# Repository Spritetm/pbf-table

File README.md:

# Pinball Fantasies physical virtual pinball table

These are the firmware, case designs, schematics and PCB artwork
for the tiny video pinball table as described [here](https://spritesmods.com?art=pftable).

# Firmware

The firmware consists of a core emulator that emulates the main game
logic, a music player to replace the audio subsystem, and bindings
for graphics, input, and audio playback for various situations.

There are three builds for the firmware:

- Host build. For this, make sure you have the SDL2 development libraries
  installed and run ``make`` ``in the esp32/components/emu`` folder. You
  should get an ``emu`` binary using that. Use lshift, rshift, F1 and 
  enter to control the emulator.
- ESP32 build for ESP-Wrover-Kit
  This needs a wrover with >=8MiB of flash (and >=2MiB of psram). Use
  ``idf.py set-target esp32`` to select this and build and flash 
  using standard esp-idf procedures. You need buttons to control these,
  for start, plunger, left flipper and right flipper respectively, 
  connect buttons from GPIO 14, 13, 15 and 12 to ground. Audio signal
  comes out of GPIO26. Note that the game does not run at full frame
  rate on an ESP32 as the code is not optimized for that chip.
- ESP32S3 on custom PCB.
  This needs the pcbs from the ``pcb/`` and ``pcb-backbox-large/`` fabricated
  and assembled. Use ``idf.py set-target esp32s3`` and build and flash
  according to standard esp-idf procedures.

Note that the ESP32 and ESP32-S3 targets also need the Pinball 
Fantasies data files flashed; the Unix build simply needs them to
exist in the data directory. Details and helpers for obtaining these
files is in the ``data/README.md`` file. There is an example script for
flashing in ``esp32/flashdata.sh``, but it may need modifying for your
particular setup.

# Case

There is a case design (made in OpenSCAD) in the ``case`` subdirectory. 
Note that the measures are mostly what works on my 3d-printer; you 
may need to print this, see if it fits, then print again to get a 
working case.

The case parts are held together by two m3 screws fitting in two 4x5mm
brass screw thread inserts. I simply super-glued the inserts in place.

# PCB

There are three folders with Kicad PCBs: ``pcb``, ``pcb-backboard`` and 
``pcb-backboard-large``. ``pcb`` contains the main PCB which fits under
the main playfield LCD. ``pcb-backboard-large`` contains the PCB I used
for the final backboard, it interfaces with a 2.3" 320x240 LCD. ``pcb-backboard``
is a previous iteration of this; it has an 1.5" 240x240 LCD on it; it 
is included for reference only.

Note: You must use an ESP32-S3 module that has 2 or more megabyte of
QUAD PSRAM onboard. A module with octal PSRAM (or octal flash) will
not function, as it needs GPIOs that are used for other things.

# Components

Most of the components are indicated on the PCBs, but some are connected
using JST-PH or JST-XH connectors. Here's a short list of what goes where:

- J2: Speaker. I used a 4 ohm, 1.5W speaker from a laptop I had around.
- J3: Connected to an 10uF MLCC SMD cap used as the plunger sensor. The 
  plunger mechanics physically hit this cap when slamming back. See
  article on how that works.
- J4: LiIon/LiPo battery. I used a generic 1000mAh, 3.7V cell I had around.
- J5: Horizontal and vertical linear haptic actuators. These actuators are
  spare parts for a Huawei Mate 30 Pro.
- J6: Flipper and start buttons. These are a 4*5.6 HD11 microswitch each.
  Note that if you use something else, you may need to change the case model
  to make them fit.

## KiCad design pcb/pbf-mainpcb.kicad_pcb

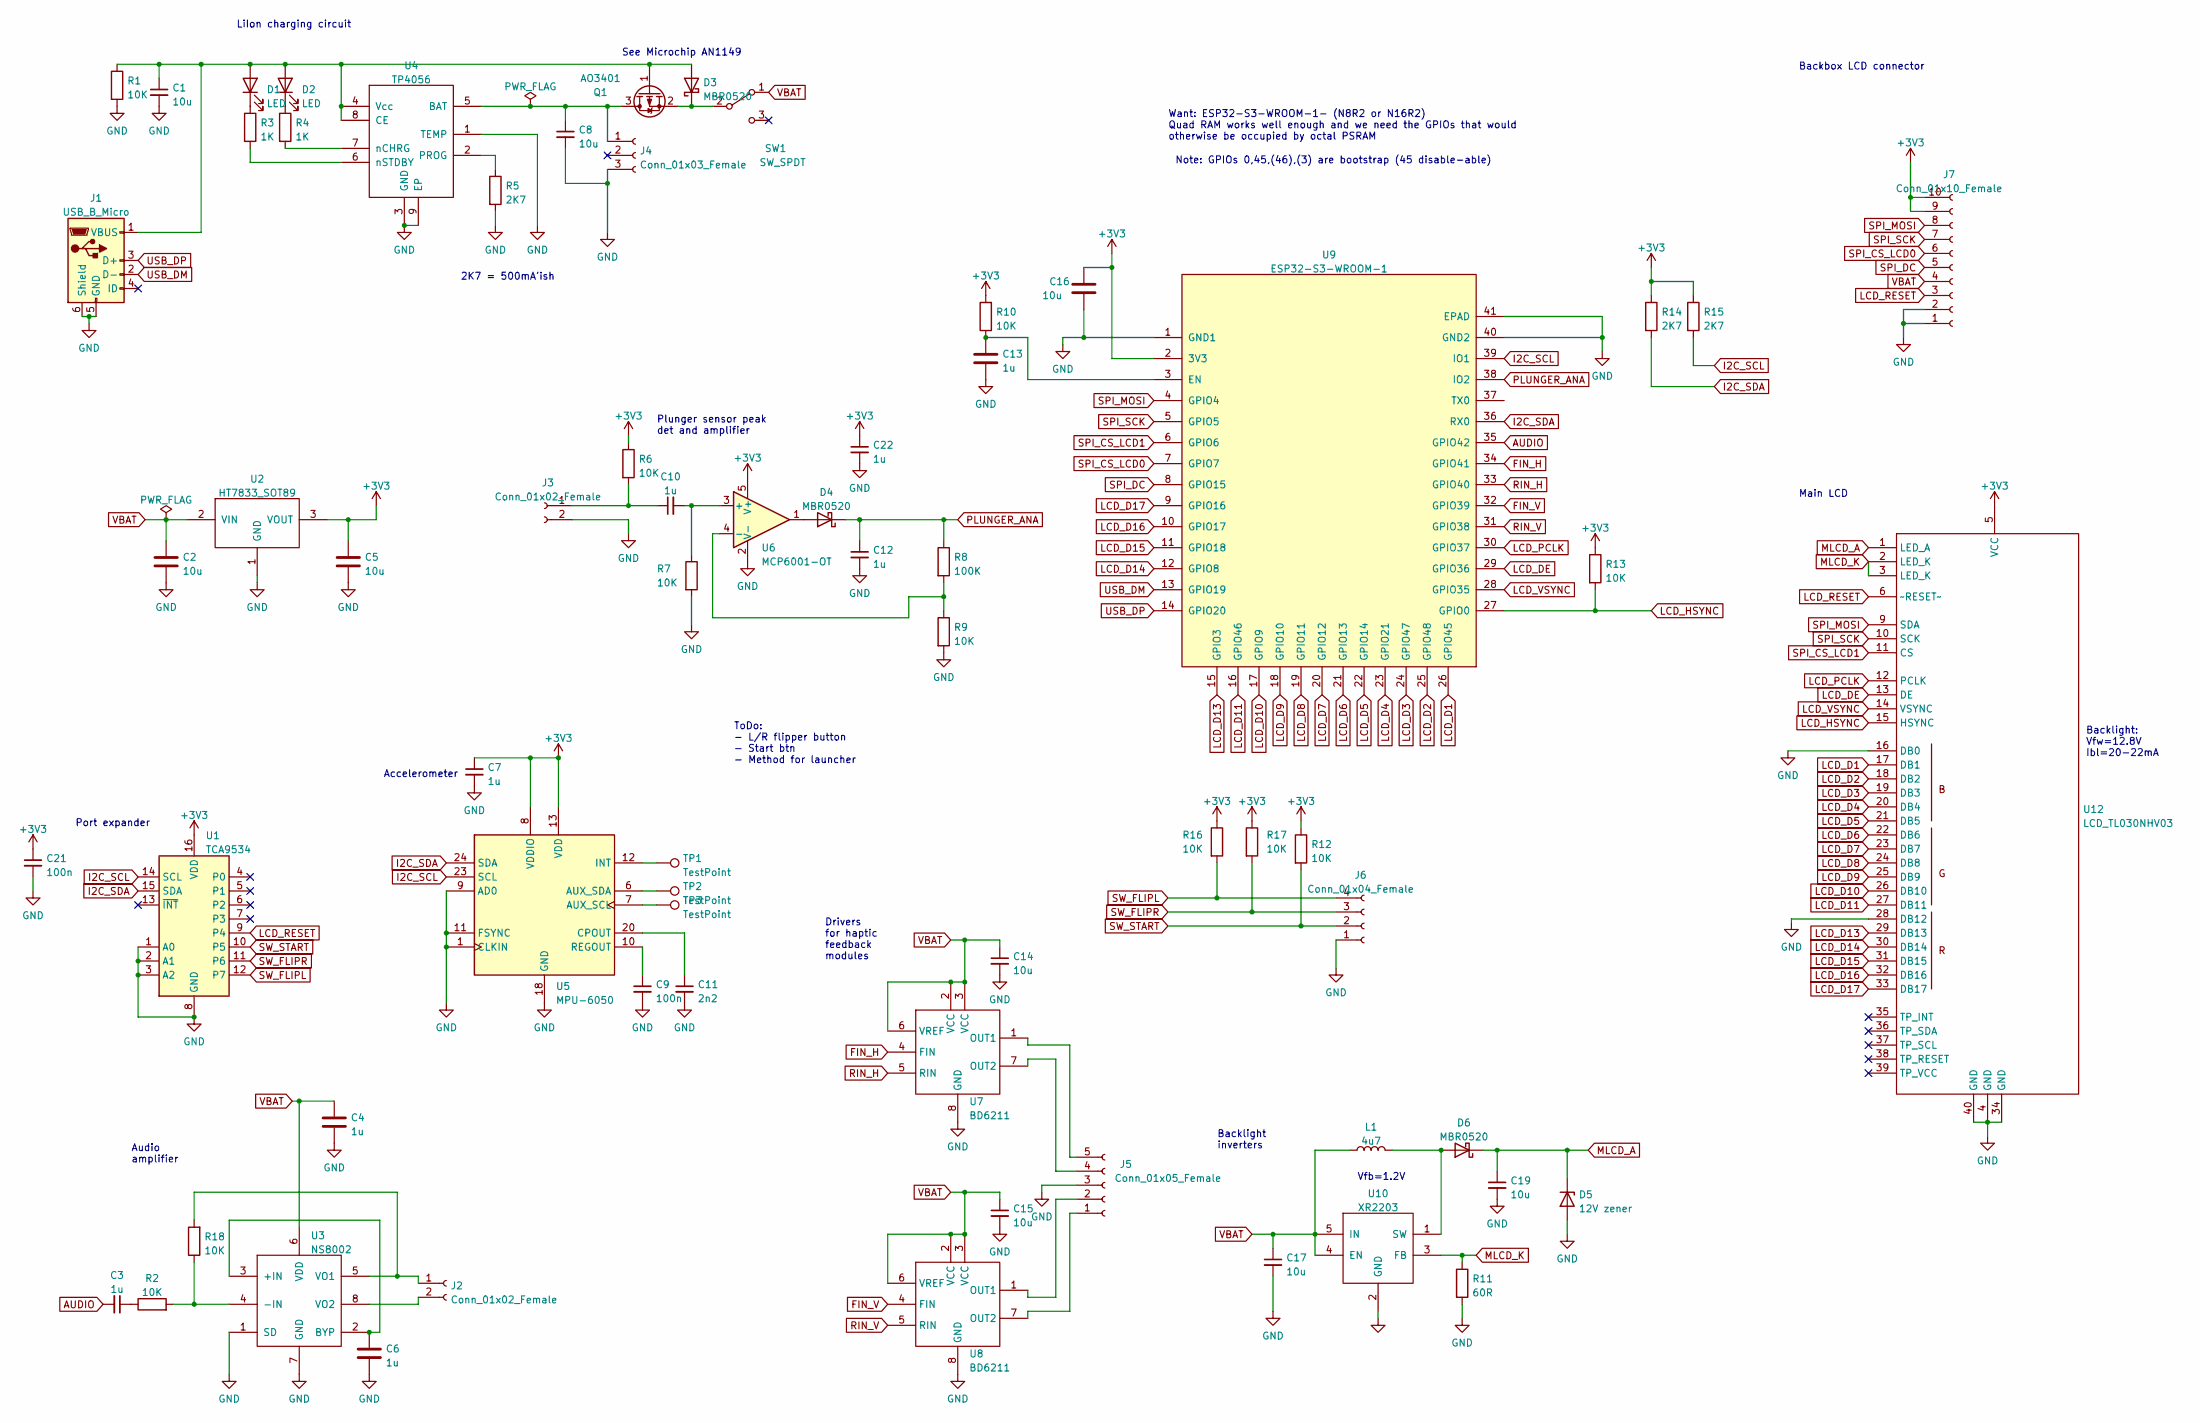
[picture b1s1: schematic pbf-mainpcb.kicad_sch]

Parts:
C1, C2, C5, C8, C14, C15, C16, C17, C19: 10u; C_0805_2012Metric
C3, C4, C6, C7, C10, C12, C13, C22: 1u; C_0603_1608Metric
C9, C21: 100n; C_0603_1608Metric
C11: 2n2; C_0603_1608Metric
D1, D2: LED; LED_0603_1608Metric
D3, D4, D6: MBR0520; D_SOD-123
D5: 12V zener; D_MELF
J1: USB_B_Micro; USB_Micro-B_China_MK5P
J2: Conn_01x02_Female; JST_XH_B2B-XH-AM_1x02_P2.50mm_Vertical
J3: Conn_01x02_Female; JST_PH_B2B-PH-K_1x02_P2.00mm_Vertical
J4: Conn_01x03_Female; JST_PH_B3B-PH-K_1x03_P2.00mm_Vertical
J5: Conn_01x05_Female; JST_PH_B5B-PH-K_1x05_P2.00mm_Vertical
J6: Conn_01x04_Female; JST_PH_B4B-PH-K_1x04_P2.00mm_Vertical
J7: Conn_01x10_Female; PinHeader_2x05_P2.54mm_Horizontal
L1: 4u7; L_1008_2520Metric
Q1: AO3401; SOT-23
R1, R2, R6, R7, R9, R10, R12, R13, R16, R17, R18: 10K; R_0603_1608Metric
R3, R4: 1K; R_0603_1608Metric
R5, R14, R15: 2K7; R_0603_1608Metric
R8: 100K; R_0603_1608Metric
R11: 60R; R_0603_1608Metric
SW1: SW_SPDT; SW_SPDT_PCM12
TP1, TP2, TP3: TestPoint; TestPoint_Pad_1.0x1.0mm
U1: TCA9534; TSSOP-16_4.4x5mm_P0.65mm
U2: HT7833_SOT89; SOT-89-3
U3: NS8002; SOP-8_3.9x4.9mm_P1.27mm
U4: TP4056; SOIC-8-1EP_3.9x4.9mm_P1.27mm_EP2.29x3mm
U5: MPU-6050; InvenSense_QFN-24_4x4mm_P0.5mm
U6: MCP6001-OT; SOT-23-5
U7, U8: BD6211; SOP-8_3.9x4.9mm_P1.27mm
U9: ESP32-S3-WROOM-1
U10: XR2203; SOT-23-5
U12: LCD_TL030NHV03; TE_4-1734839-0_1x40-1MP_P0.5mm_Horizontal_Reversed

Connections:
+3V3: C5.1, C7.1, C16.1, C21.1, C22.1, J7.9, J7.10, R6.1, R10.2, R12.1, R13.1, R14.1, R15.1, R16.1, R17.1, U1.16 (VDD), U2.3 (VOUT), U5.8 (VDDIO), U5.13 (VDD), U6.5 (V+), U9.2 (3V3), U12.5 (VCC)
AUDIO: C3.2, U9.35 (GPIO42)
FIN_H: U7.4 (FIN), U9.34 (GPIO41)
FIN_V: U8.4 (FIN), U9.32 (GPIO39)
I2C_SCL: R15.2, U1.14 (SCL), U5.23 (SCL), U9.39 (IO1)
I2C_SDA: R14.2, U1.15 (SDA), U5.24 (SDA), U9.36 (RX0)
LCD_D1: U9.26 (GPIO45), U12.17 (DB1)
LCD_D2: U9.25 (GPIO48), U12.18 (DB2)
LCD_D3: U9.24 (GPIO47), U12.19 (DB3)
LCD_D4: U9.23 (GPIO21), U12.20 (DB4)
LCD_D5: U9.22 (GPIO14), U12.21 (DB5)
LCD_D6: U9.21 (GPIO13), U12.22 (DB6)
LCD_D7: U9.20 (GPIO12), U12.23 (DB7)
LCD_D8: U9.19 (GPIO11), U12.24 (DB8)
LCD_D9: U9.18 (GPIO10), U12.25 (DB9)
LCD_D10: U9.17 (GPIO9), U12.26 (DB10)
LCD_D11: U9.16 (GPIO46), U12.27 (DB11)
LCD_D13: U9.15 (GPIO3), U12.29 (DB13)
LCD_D14: U9.12 (GPIO8), U12.30 (DB14)
LCD_D15: U9.11 (GPIO18), U12.31 (DB15)
LCD_D16: U9.10 (GPIO17), U12.32 (DB16)
LCD_D17: U9.9 (GPIO16), U12.33 (DB17)
LCD_DE: U9.29 (GPIO36), U12.13 (DE)
LCD_HSYNC: R13.2, U9.27 (GPIO0), U12.15 (HSYNC)
LCD_PCLK: U9.30 (GPIO37), U12.12 (PCLK)
LCD_RESET: J7.3, U1.9 (P4), U12.6 (~RESET~)
LCD_VSYNC: U9.28 (GPIO35), U12.14 (VSYNC)
MLCD_A: C19.1, D5.1 (K), D6.1 (K), U12.1 (LED_A)
MLCD_K: R11.1, U10.3 (FB), U12.2 (LED_K), U12.3 (LED_K)
unnamed: C1.1, D1.2 (A), D2.2 (A), D3.2 (A), J1.1 (VBUS), Q1.1 (G), R1.1, U4.4 (Vcc), U4.8 (CE)
unnamed: C3.1, R2.1
unnamed: C6.1, U3.2 (BYP), U3.3 (+IN)
unnamed: C8.1, J4.1, Q1.3 (D), U4.5 (BAT)
unnamed: C9.1, U5.10 (REGOUT)
unnamed: C10.1, J3.1, R6.2
unnamed: C10.2, R7.1, U6.3 (+)
unnamed: C11.1, U5.20 (CPOUT)
unnamed: C13.1, R10.1, U9.3 (EN)
unnamed: D1.1 (K), R3.1
unnamed: D2.1 (K), R4.1
unnamed: D3.1 (K), Q1.2 (S), SW1.2 (B)
unnamed: D4.2 (A), U6.1
unnamed: D6.2 (A), L1.2, U10.1 (SW)
unnamed: J2.1, R18.2, U3.5 (VO1)
unnamed: J2.2, U3.8 (VO2)
unnamed: J5.1, U8.7 (OUT2)
unnamed: J5.2, U8.1 (OUT1)
unnamed: J5.4, U7.7 (OUT2)
unnamed: J5.5, U7.1 (OUT1)
unnamed: R3.2, U4.6 (nSTDBY)
unnamed: R4.2, U4.7 (nCHRG)
unnamed: R5.1, U4.2 (PROG)
unnamed: R8.2, R9.1, U6.4 (-)
unnamed: TP1.1, U5.12 (INT)
unnamed: TP2.1, U5.6 (AUX_SDA)
unnamed: TP3.1, U5.7 (AUX_SCL)
unnamed: R2.2, R18.1, U3.4 (-IN)
PLUNGER_ANA: C12.1, D4.1 (K), R8.1, U9.38 (IO2)
RIN_H: U7.5 (RIN), U9.33 (GPIO40)
RIN_V: U8.5 (RIN), U9.31 (GPIO38)
SPI_CS_LCD0: J7.6, U9.7 (GPIO7)
SPI_CS_LCD1: U9.6 (GPIO6), U12.11 (CS)
SPI_DC: J7.5, U9.8 (GPIO15)
SPI_MOSI: J7.8, U9.4 (GPIO4), U12.9 (SDA)
SPI_SCK: J7.7, U9.5 (GPIO5), U12.10 (SCK)
SW_FLIPL: J6.4, R16.2, U1.12 (P7)
SW_FLIPR: J6.3, R17.2, U1.11 (P6)
SW_START: J6.2, R12.2, U1.10 (P5)
USB_DM: J1.2 (D-), U9.13 (GPIO19)
USB_DP: J1.3 (D+), U9.14 (GPIO20)
VBAT: C2.1, C4.1, C14.1, C15.1, C17.1, J7.4, L1.1, SW1.1 (A), U2.2 (VIN), U3.6 (VDD), U7.2 (VCC), U7.3 (VCC), U7.6 (VREF), U8.2 (VCC), U8.3 (VCC), U8.6 (VREF), U10.4 (EN), U10.5 (IN)

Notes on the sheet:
Plunger sensor peak det and amplifier
Port expander
Backbox LCD connector
ToDo: - L/R flipper button - Start btn - Method for launcher
Vfb=1.2V
Backlight inverters
LiIon charging circuit
Main LCD
Accelerometer
2K7 = 500mA'ish
Audio amplifier
Want: ESP32-S3-WROOM-1- (N8R2 or N16R2) Quad RAM works well enough and we need the GPIOs that would otherwise be occupied by octal PSRAM
Backlight: Vfw=12.8V Ibl=20-22mA
Drivers for haptic feedback modules
See Microchip AN1149
Note: GPIOs 0,45,(46),(3) are bootstrap (45 disable-able)

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
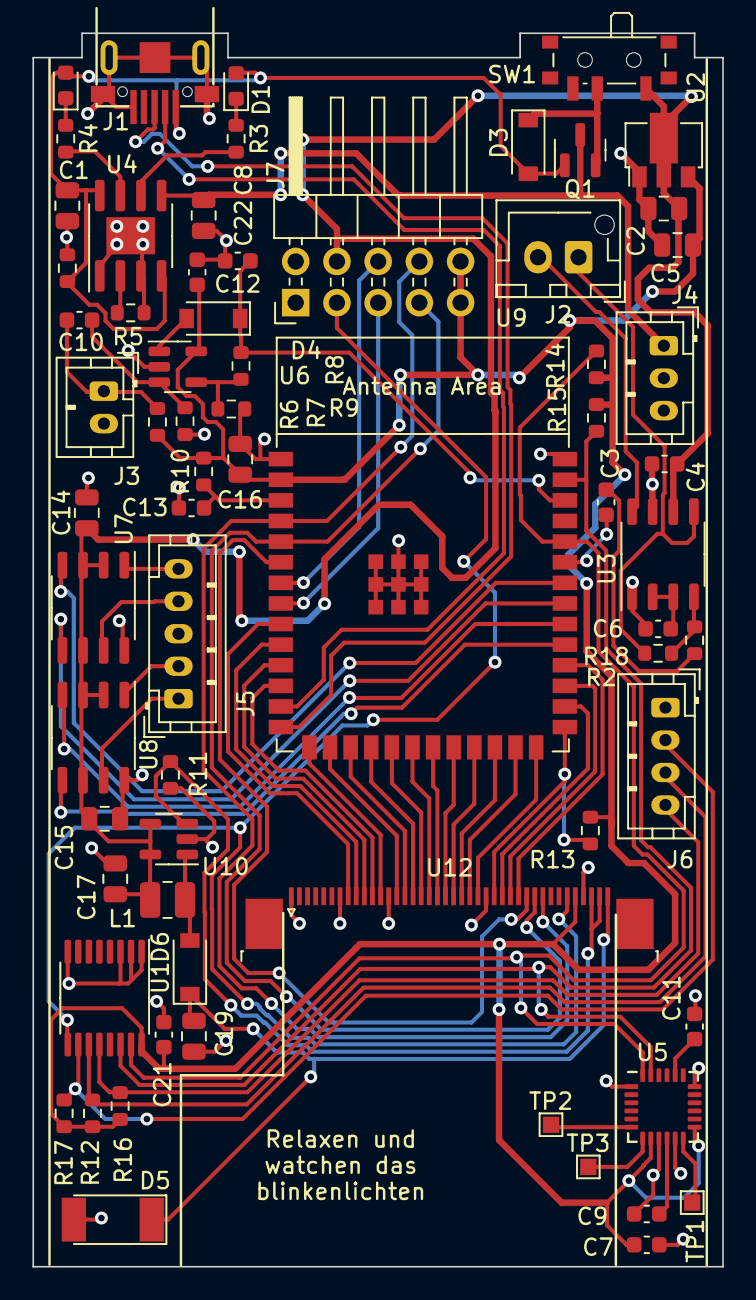
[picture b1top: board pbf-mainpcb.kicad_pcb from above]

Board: 2 copper layers, 42.5 x 76.0 mm, 68 parts (0 on the bottom side), 72 nets.

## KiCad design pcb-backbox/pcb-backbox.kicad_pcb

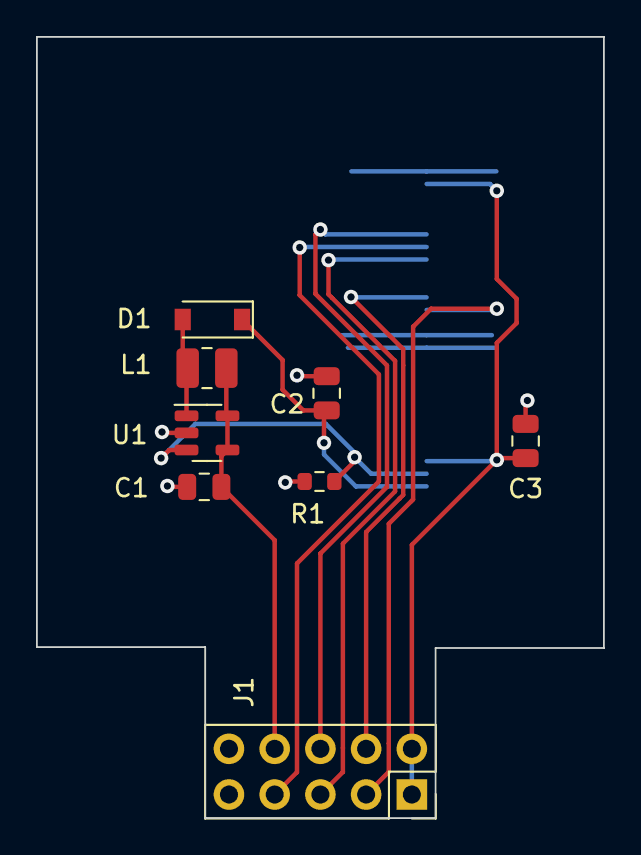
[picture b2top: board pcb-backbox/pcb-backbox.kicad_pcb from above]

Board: 2 copper layers, 31.5 x 43.4 mm, 9 parts (1 on the bottom side), 11 nets.

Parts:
C1, C2, C3: 10u; C_0805_2012Metric
CON1: 1.5IN_DISP_240x240; lcd_1.5in_vert_hotbar
D1: MBR0520; D_SOD-123
J1: Conn_01x10_Male; PinSocket_2x05_P2.54mm_Vertical
L1: 4u7; L_1008_2520Metric
R1: 27R; R_0603_1608Metric
U1: XR2203; SOT-23-5

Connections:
+3V3: C3.1, CON1.9 (VIO_1V8), CON1.31 (VDD28), J1.1, J1.2
BLCD_A: C2.1, CON1.33 (LEDA+), D1.1 (K)
BLCD_K: CON1.32 (LEDK-), R1.1, U1.3 (FB)
GND: C1.2, C2.2, C3.2, CON1.8 (VSS), CON1.21 (VSS), CON1.22 (VSS), J1.9, J1.10, R1.2, U1.2 (GND)
LCD_RESET: CON1.14 (~RESET), J1.7
unnamed: D1.2 (A), L1.2, U1.1 (SW)
SPI_CS_LCD0: CON1.13 (~CS), J1.6
SPI_DC: CON1.15 (A0), J1.5
SPI_MOSI: CON1.18 (SCL), J1.4
SPI_SCK: CON1.19 (SDA), J1.3
VBAT: C1.1, J1.8, L1.1, U1.4 (EN), U1.5 (IN)

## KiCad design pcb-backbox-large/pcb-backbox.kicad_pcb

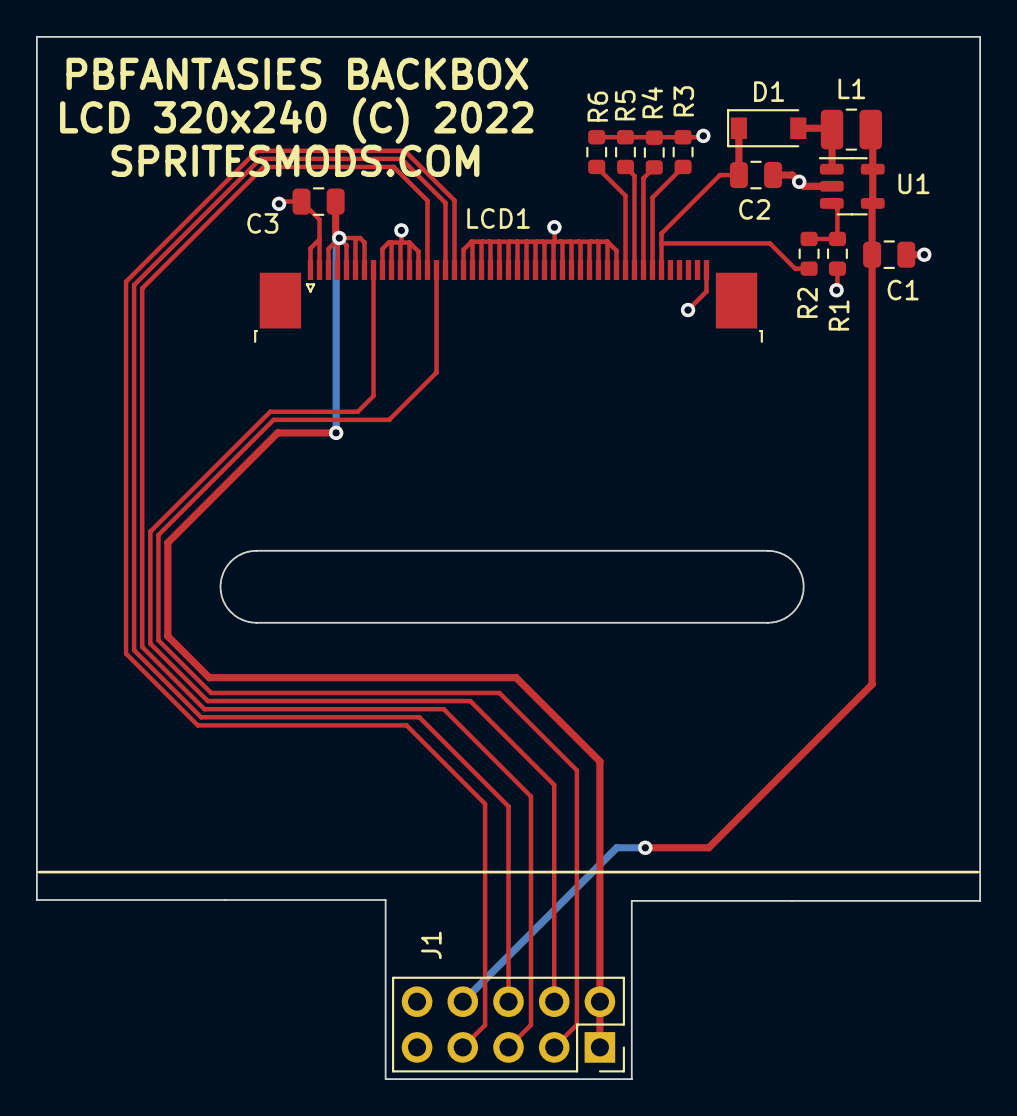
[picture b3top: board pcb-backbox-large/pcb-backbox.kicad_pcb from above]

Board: 2 copper layers, 52.4 x 57.9 mm, 14 parts (0 on the bottom side), 15 nets.

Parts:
C1, C2, C3: 10u; C_0805_2012Metric
D1: MBR0520; D_SOD-123
J1: Conn_01x10_Male; PinSocket_2x05_P2.54mm_Vertical
L1: 4u7; L_1008_2520Metric
LCD1: KD023C-1; TE_4-1734839-5_1x45-1MP_P0.5mm_Horizontal
R1: 33K; R_0603_1608Metric
R2: 100K; R_0603_1608Metric
R3, R4, R5, R6: 270; R_0603_1608Metric
U1: XR2203; SOT-23-5

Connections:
+3V3: C3.1, J1.1, J1.2, LCD1.3 (VCI), LCD1.4 (VCI), LCD1.5 (IM3), LCD1.6 (IM1), LCD1.7 (IM0)
BLCD_A: C2.1, D1.1 (K), LCD1.40 (LEDA), R2.1
GND: C1.2, C2.2, C3.2, J1.9, J1.10, LCD1.1 (GND), LCD1.2 (GND), LCD1.9 (VSYNC), LCD1.10 (HSYNC), LCD1.11 (DOTCLK), LCD1.12 (ENABLE), LCD1.13 (RD), LCD1.18 (DB17), LCD1.19 (DB16), LCD1.20 (DB15), LCD1.21 (DB14), LCD1.22 (DB13), LCD1.23 (DB12), LCD1.24 (DB11), LCD1.25 (DB10), LCD1.26 (DB9), LCD1.27 (DB8), LCD1.28 (DB7), LCD1.29 (DB6), LCD1.30 (DB5), LCD1.31 (DB4), LCD1.32 (DB3), LCD1.33 (DB2), LCD1.34 (DB1), LCD1.35 (DB0), LCD1.45 (GND), R1.2, R3.1, R4.1, R5.1, R6.1, U1.2 (GND)
LCD_RESET: J1.7, LCD1.17 (RESET)
unnamed: D1.2 (A), L1.2, U1.1 (SW)
unnamed: LCD1.36 (LEDK1), R6.2
unnamed: LCD1.37 (LEDK2), R5.2
unnamed: LCD1.38 (LEDK3), R4.2
unnamed: LCD1.39 (LEDK4), R3.2
unnamed: R1.1, R2.2, U1.3 (FB)
SPI_CS_LCD0: J1.6, LCD1.16 (CS)
SPI_DC: J1.5, LCD1.14 (WR/SPI_RS)
SPI_MOSI: J1.4, LCD1.8 (SDA)
SPI_SCK: J1.3, LCD1.15 (RS/SPI_SCL)
VBAT: C1.1, J1.8, L1.1, U1.4 (EN), U1.5 (IN)

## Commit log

2022-01-27 Emu works, we get some gfx
2022-01-29 Properly do video sync and size
2022-01-29 Add fragmented address space, to save RAM
2022-01-29 Add mod playing
2022-01-30 Add keyboard, fix audio
2022-02-09 Hmm? Matrix goes a bit further.
2022-03-19 Try to get the stupid pinball emu to not b0rk after starting a game...
2022-03-19 Omg, found the bug, it was in the line that checks if a callback has ended yet. Anyway, the frantic debugging session also lead to some refactoring and cleaning up, so not all is lost.
2022-03-19 Clean up a bit, add prefs
2022-03-20 Start of modifications into an esp-idf project
2022-03-20 Convert into esp32 project
2022-03-22 Buttons
2022-03-24 Move some CPU fns to IRAM, optimize a bit
2022-03-24 Optimize: put stuff in IRAM, move hot sections of x86 in RAM pre-emptively, take time spent in callback into account for callback
2022-03-27 Add code to glean internal vars from PF binary
2022-04-20 Move to octal psram
2022-04-20 abort test
2022-04-20 Code runs, and even runs well!
2022-04-21 Yay, 60fps
2022-04-30 WiP: move music to separate file
2022-05-02 Emu works, backboard LCD is barebones but works, added menu
2022-05-02 DMD scaling on bb lcd
2022-05-03 Highscore entering & saving works
2022-05-14 Add plunger, small cleanup
2022-06-17 fix esp32, add table images to bin
2022-06-24 esp32 code fix; move to new hardware
2022-06-24 Convert to 320x240 backbox LCD
2022-07-06 Add other haptic thing
2022-07-09 Restructure repo to entire project; add PCB artwork
2022-07-09 Add original pinball fantasies sources
2022-07-09 Add instructions on how to extract pbf data files
2022-07-09 Add licenses
2022-07-09 Split sdkconfig into defaults for esp32 and esp32s3
2022-07-09 Add OpenSCAD case design
2022-07-09 add some notes
2022-07-09 Add config screen, allow for plunger calibration
2022-07-09 Add support for tilting the table using accelerometer
2022-07-09 Backbox: show hiscores on table select screen
2022-07-10 Cleanup, add comments while I still remember what the code does
2022-07-10 add more readme
2022-07-10 Add pdf versions of schematics
2022-07-17 Fix things I bodged in my prototype
2023-12-05 added readme description, changed zener 12V -> 15V
2023-12-07 added vscode support
2023-12-07 port to esp-idf 5.0.4
2023-12-11 Fix porting issues; update audio driver to new api
2023-12-11 Make it more clearer that you cannot use octal psram
2023-12-17 Make compatible with older esp-idf v5.0.x versions
2023-12-17 Try to autodetect tca9534 and tca9534a chips

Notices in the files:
pcb-backbox-large/pcb-backbox.kicad_pcb:
LCD 320x240 (C) 2022
pcb/pbf-mainpcb.kicad_pcb:
(C) 2022 Spritesmods.com
